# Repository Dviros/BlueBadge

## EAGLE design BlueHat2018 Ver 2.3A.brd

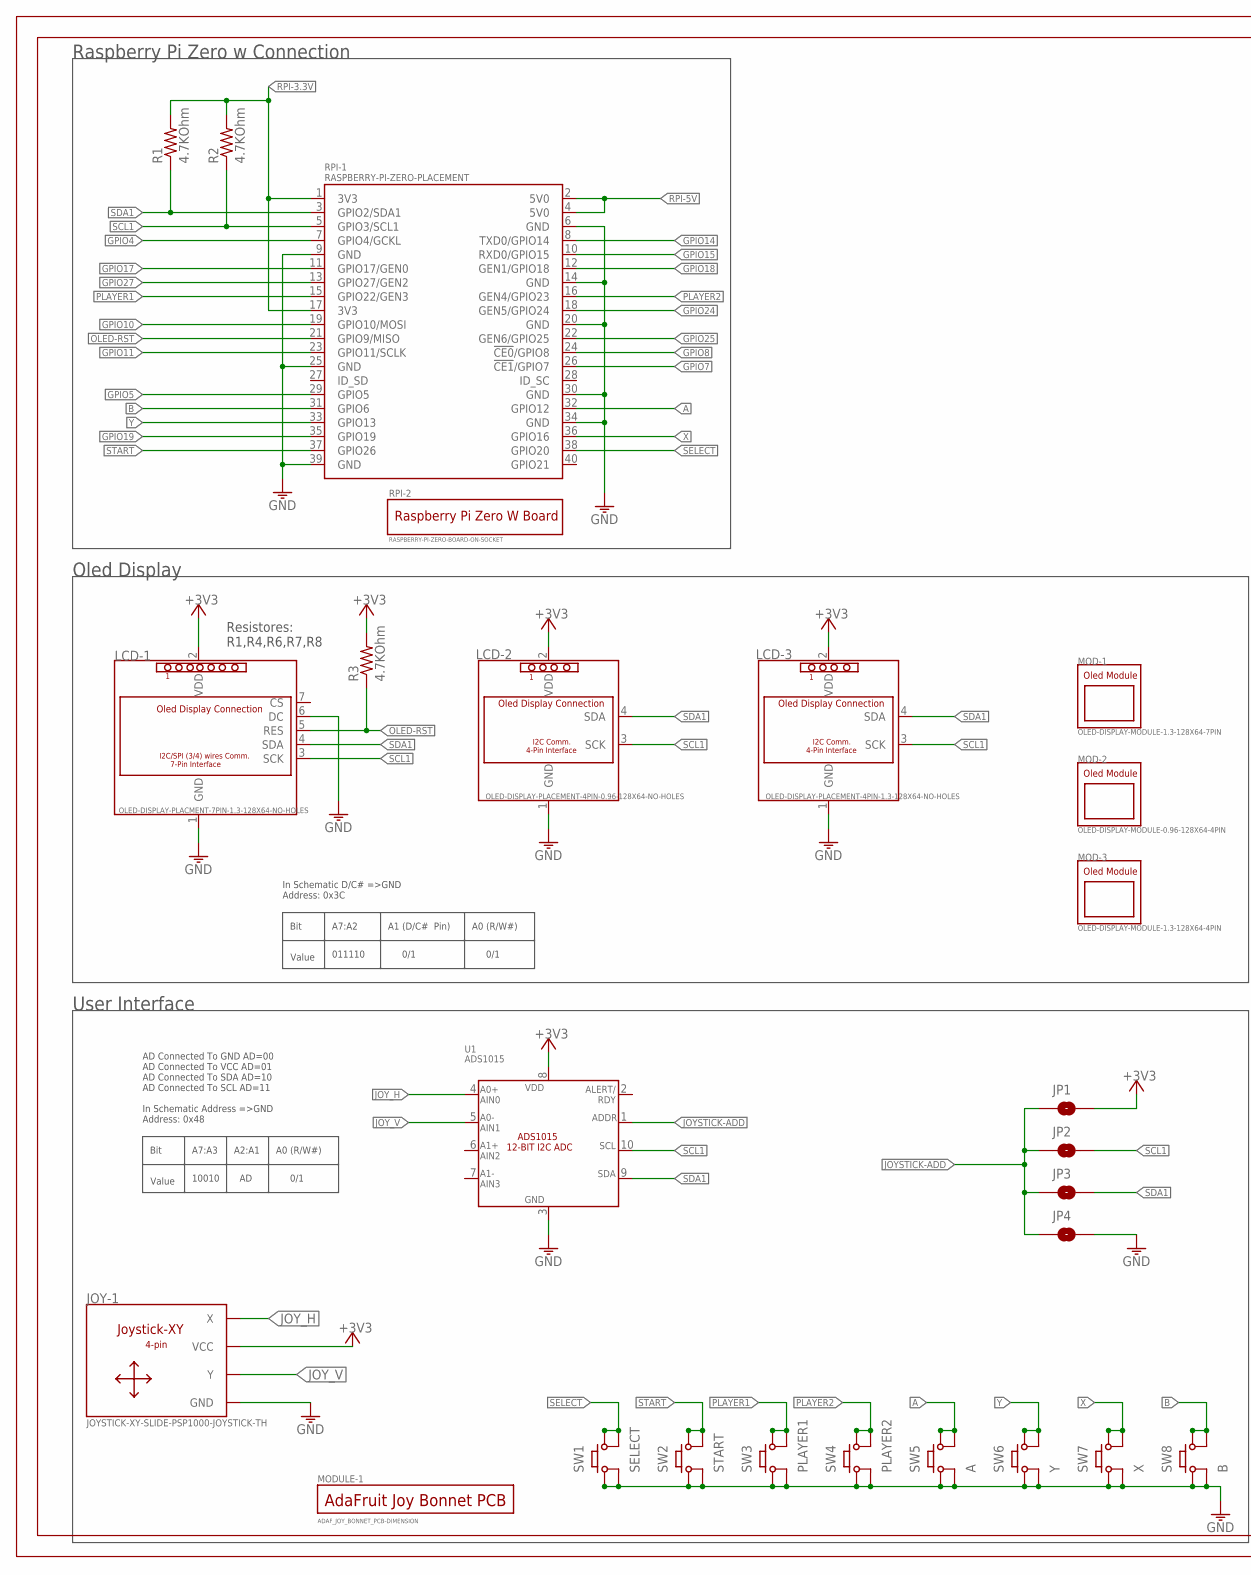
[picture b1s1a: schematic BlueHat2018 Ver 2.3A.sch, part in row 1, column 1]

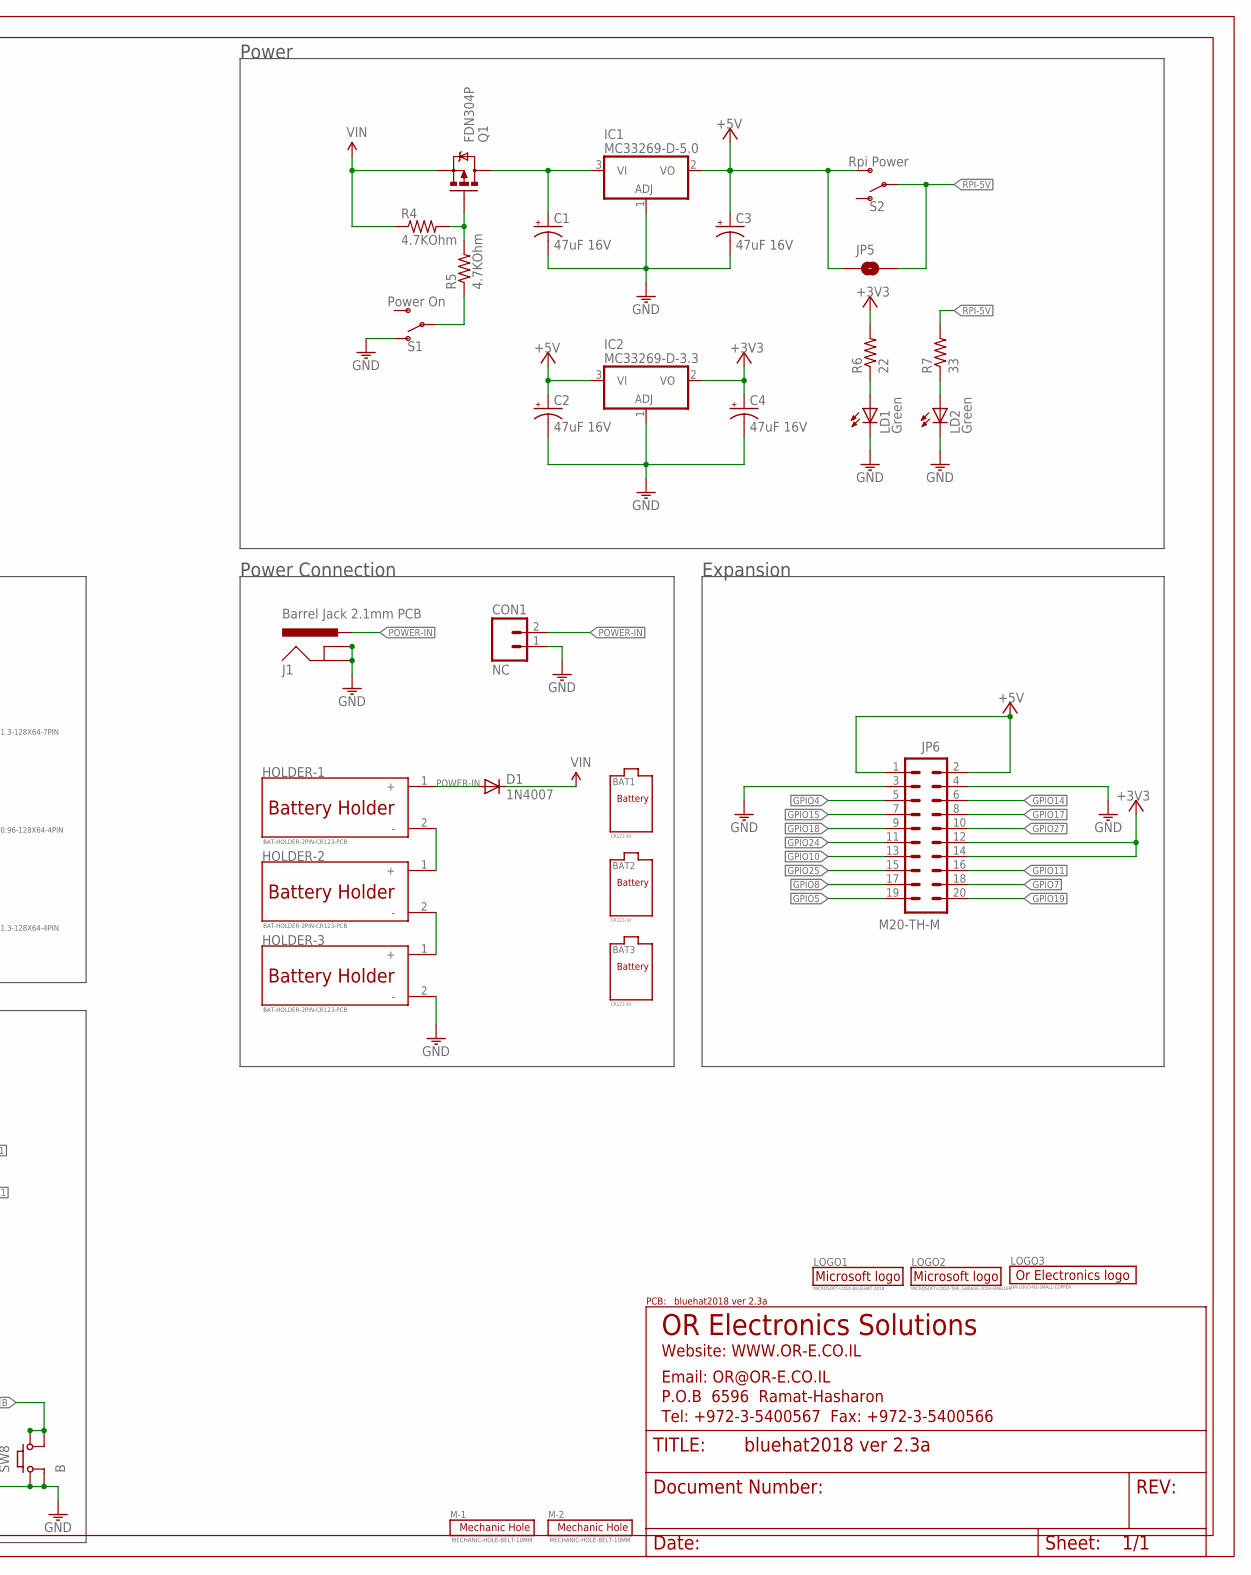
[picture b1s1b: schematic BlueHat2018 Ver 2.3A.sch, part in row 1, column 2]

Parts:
BAT1, BAT2, BAT3: CR123-3V; CR123-BATTERY
C1, C2, C3, C4: 47uF 16V; PANASONIC_D
CON1: NC; 1X02-TH-M
D1: 1N4007; DO214AC
FRAME1: FRAME_B_L-TDOC; PCB_DRAW_NAME_TDOC
HOLDER-1, HOLDER-2, HOLDER-3: BAT-HOLDER-2PIN-CR123-PCB; BAT-CR123-HOLDER
IC1: MC33269-D-5.0; DPACK
IC2: MC33269-D-3.3; DPACK
J1: Barrel Jack 2.1mm PCB; POWER_JACK_PTH_LOCK
JOY-1: JOYSTICK-XY-SLIDE-PSP1000-JOYSTICK-TH; JOYSTICK-PSP1000-TH
JP1, JP2, JP3, JP5: JUMPER-2-POSITION-SMD-NO; SJ_2S-NO
JP4: JUMPER-2-POSITION-SMD-NC-TRACE-SMALL; SJ_2S-TRACE-SMALL
JP6: M20-TH-M; 2X10-TH-M
LCD-1: OLED-DISPLAY-PLACMENT-7PIN-1.3-128X64-NO-HOLES; OLED-1.3-7PIN-NO-HOLES
LCD-2: OLED-DISPLAY-PLACEMENT-4PIN-0.96-128X64-NO-HOLES; OLED-0.96-4PIN-NO-HOLES
LCD-3: OLED-DISPLAY-PLACEMENT-4PIN-1.3-128X64-NO-HOLES; OLED-1.3-4PIN-NO-HOLES
LD1, LD2: Green; LD0603
LOGO1: MICROSOFT-LOGO-BLUEHAT-2018; MICROSOFT_LOGO1_2018
LOGO2: MICROSOFT-LOGO-THE_GARAGE-2018-SMALLER; MICROSOFT_LOGO2_2018_SMALLER
LOGO3: OR-LOGO-NS-SMALL-COPPER; OR_LOGO-NS-SMALL-COPPER
M-1, M-2: MECHANIC-HOLE-BELT-10MM; BELT-10MM
MOD-1: OLED-DISPLAY-MODULE-1.3-128X64-7PIN; OLED-MODULE-1.3-128X64-7PIN
MOD-2: OLED-DISPLAY-MODULE-0.96-128X64-4PIN; OLED-MODULE-0.96-128X64-4PIN
MOD-3: OLED-DISPLAY-MODULE-1.3-128X64-4PIN; OLED-MODULE-1.3-128X64-4PIN
MODULE-1: ADAF_JOY_BONNET_PCB-DIMENSION; ADAF_JOY_BONNET_DIMENSION.
Q1: FDN304P; SOT23
R1, R2, R3, R4, R5: 4.7KOhm; R0805
R6: 22; R0805
R7: 33; R0805
RPI-1: RASPBERRY-PI-ZERO-PLACEMENT; RPI_ZERO_BOARD_PLACEMENT
RPI-2: RASPBERRY-PI-ZERO-BOARD-ON-SOCKET
S1: Power On; ALPS-SSSS820201
S2: Rpi Power; ALPS-SSSS820201
SW1: SELECT; TACTILE-6X6-PTH
SW2: START; TACTILE-6X6-PTH
SW3: PLAYER1; TACTILE-6X6-PTH
SW4: PLAYER2; TACTILE-6X6-PTH
SW5: A; TACTILE-6X6-PTH
SW6: Y; TACTILE-6X6-PTH
SW7: X; TACTILE-6X6-PTH
SW8: B; TACTILE-6X6-PTH
U1: ADS1015; MSOP10

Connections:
+3V3: C4.+, IC2.2 (VO), JOY-1.VCC, JOY-1.VCC@1 (VCC), JP1.2, JP6.12, JP6.14, LCD-1.2 (VDD), LCD-2.2 (VDD), LCD-3.2 (VDD), R3.2, R6.2, U1.8 (VDD)
+5V: C2.+, C3.+, IC1.2 (VO), IC2.3 (VI), JP5.1, JP6.1, JP6.2, S2.3 (T2)
A: RPI-1.32 (GPIO12), SW5.3, SW5.4
B: RPI-1.31 (GPIO6), SW8.3, SW8.4
GND: C1.-, C2.-, C3.-, C4.-, CON1.1, HOLDER-3.2 (-), IC1.1 (ADJ), IC2.1 (ADJ), J1.GND, J1.GNDBREAK, JOY-1.GND, JOY-1.GND@1 (GND), JP4.2, JP6.3, JP6.4, LCD-1.1 (GND), LCD-1.6 (DC), LCD-2.1 (GND), LCD-3.1 (GND), LD1.C, LD2.C, S1.1 (T1), SW1.1, SW1.2, SW2.1, SW2.2, SW3.1, SW3.2, SW4.1, SW4.2, SW5.1, SW5.2, SW6.1, SW6.2, SW7.1, SW7.2, SW8.1, SW8.2, U1.3 (VSS)
GND@3: RPI-1.9 (GND), RPI-1.25 (GND), RPI-1.39 (GND)
GND@7: RPI-1.6 (GND), RPI-1.14 (GND), RPI-1.20 (GND), RPI-1.30 (GND), RPI-1.34 (GND)
GPIO4: JP6.5, RPI-1.7 (GPIO4/GCKL)
GPIO5: JP6.19, RPI-1.29 (GPIO5)
GPIO7: JP6.18, RPI-1.26 (!CE1!/GPIO7)
GPIO8: JP6.17, RPI-1.24 (!CE0!/GPIO8)
GPIO10: JP6.13, RPI-1.19 (GPIO10/MOSI)
GPIO11: JP6.16, RPI-1.23 (GPIO11/SCLK)
GPIO14: JP6.6, RPI-1.8 (TXD0/GPIO14)
GPIO15: JP6.7, RPI-1.10 (RXD0/GPIO15)
GPIO17: JP6.8, RPI-1.11 (GPIO17/GEN0)
GPIO18: JP6.9, RPI-1.12 (GEN1/GPIO18)
GPIO19: JP6.20, RPI-1.35 (GPIO19)
GPIO24: JP6.11, RPI-1.18 (GEN5/GPIO24)
GPIO25: JP6.15, RPI-1.22 (GEN6/GPIO25)
GPIO27: JP6.10, RPI-1.13 (GPIO27/GEN2)
JOYSTICK-ADD: JP1.1, JP2.1, JP3.1, JP4.1, U1.1 (ADDR)
JOY_H: JOY-1.X, JOY-1.X@1 (X), U1.4 (AIN0)
JOY_V: JOY-1.Y, JOY-1.Y@1 (Y), U1.5 (AIN1)
unnamed: HOLDER-1.2 (-), HOLDER-2.1 (+)
unnamed: C1.+, IC1.3 (VI), Q1.3 (D)
unnamed: Q1.1 (G), R4.2, R5.2
unnamed: LD1.A, R6.1
unnamed: LD2.A, R7.1
unnamed: R5.1, S1.2
unnamed: HOLDER-2.2 (-), HOLDER-3.1 (+)
OLED-RST: LCD-1.5 (RES), R3.1, RPI-1.21 (GPIO9/MISO)
PLAYER1: RPI-1.15 (GPIO22/GEN3), SW3.3, SW3.4
PLAYER2: RPI-1.16 (GEN4/GPIO23), SW4.3, SW4.4
POWER-IN: CON1.2, D1.A, HOLDER-1.1 (+), J1.PWR
RPI-3.3V: R1.2, R2.2, RPI-1.1 (3V3), RPI-1.17 (3V3)
RPI-5V: JP5.2, R7.2, RPI-1.2 (5V0), RPI-1.4 (5V0), S2.2
SCL1: JP2.2, LCD-1.3 (SCK), LCD-2.3 (SCK), LCD-3.3 (SCK), R2.1, RPI-1.5 (GPIO3/SCL1), U1.10 (SCL)
SDA1: JP3.2, LCD-1.4 (SDA), LCD-2.4 (SDA), LCD-3.4 (SDA), R1.1, RPI-1.3 (GPIO2/SDA1), U1.9 (SDA)
SELECT: RPI-1.38 (GPIO20), SW1.3, SW1.4
START: RPI-1.37 (GPIO26), SW2.3, SW2.4
VIN: D1.C, Q1.2 (S), R4.1
X: RPI-1.36 (GPIO16), SW7.3, SW7.4
Y: RPI-1.33 (GPIO13), SW6.3, SW6.4

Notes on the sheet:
Expansion
User Interface
Raspberry Pi Zero w Connection
AD Connected To GND AD=00 AD Connected To VCC AD=01 AD Connected To SDA AD=10 AD Connected To SCL AD=11 In Schematic Address =>GND Address: 0x48
Bit
Value
A7:A3
10010
A2:A1
A0 (R/W#)
0/1
Oled Display
Power Connection
Power
Resistores: R1,R4,R6,R7,R8
A7:A2
011110
A1 (D/C# Pin)
In Schematic D/C# =>GND Address: 0x3C

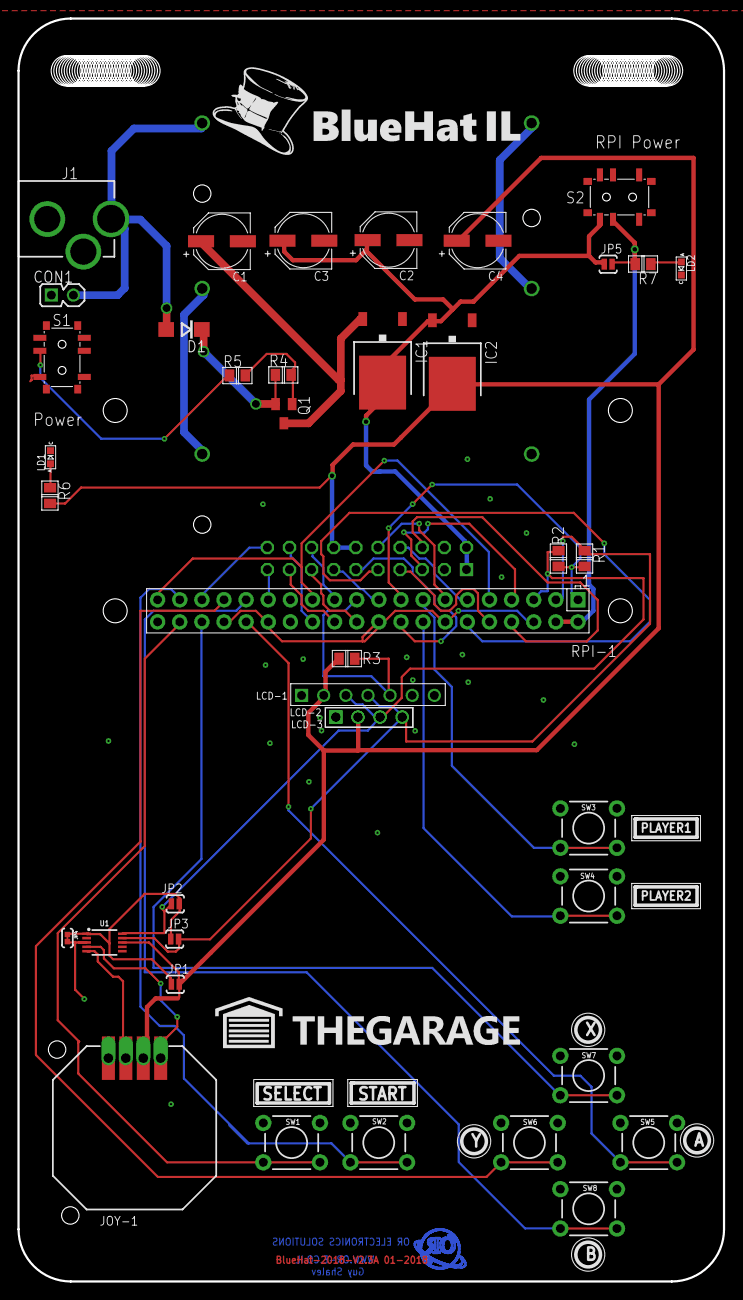
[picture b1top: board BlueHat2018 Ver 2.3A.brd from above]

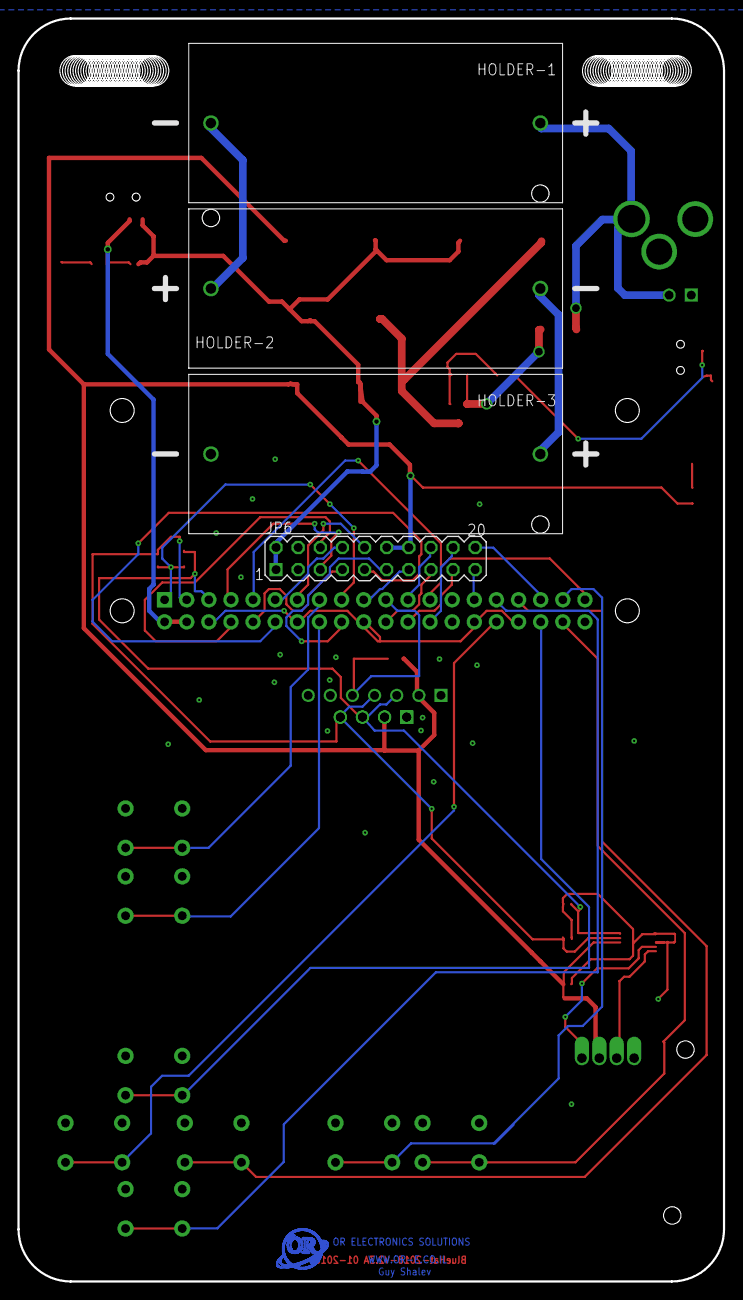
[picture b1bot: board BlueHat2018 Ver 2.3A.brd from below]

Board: 2 copper layers, 81.0 x 145.0 mm, 58 parts (8 on the bottom side), 44 nets.

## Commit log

2018-01-25 deisgn files
